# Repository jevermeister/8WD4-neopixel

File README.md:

This is a PCB which replaces the default one on Siemens 8WD4 signal tower lights with a SK6812 neopixel. 
Documentation is in the works.

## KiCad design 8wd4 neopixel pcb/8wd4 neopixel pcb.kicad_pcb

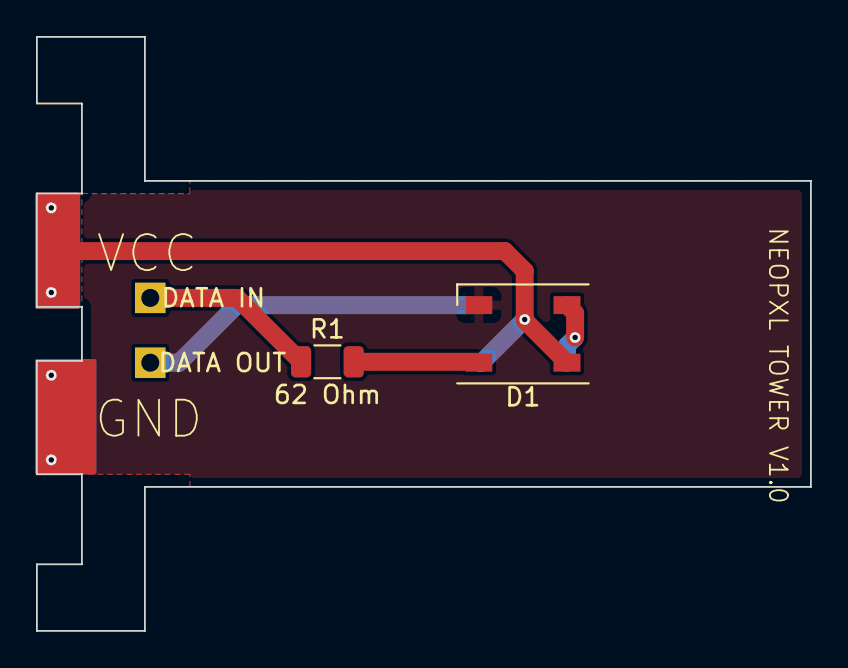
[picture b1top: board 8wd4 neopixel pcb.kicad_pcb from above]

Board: 2 copper layers, 43.0 x 33.0 mm, 5 parts (1 on the bottom side), 6 nets.

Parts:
D1, D2: SK6812; LED_SK6812_PLCC4_5.0x5.0mm_P3.2mm
DATA IN: DATA_IN; PinHeader_1x01_P2.54mm_Vertical
DATA OUT: DATA_OUT; PinHeader_1x01_P2.54mm_Vertical
R1: 62 Ohm; R_1206_3216Metric

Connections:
+5V: D1.3 (VDD), D2.3 (VDD)
GND: D1.1 (VSS), D2.1 (VSS)
unnamed: D1.2 (DIN), R1.2
unnamed: D1.4 (DOUT), D2.2 (DIN)
unnamed: D2.4 (DOUT), DATA OUT.1
unnamed: DATA IN.1, R1.1

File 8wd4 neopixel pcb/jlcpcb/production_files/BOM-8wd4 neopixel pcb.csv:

Comment,Designator,Footprint,LCSC
62 Ohm,R1,R_1206_3216Metric,
SK6812,D1,LED_SK6812_PLCC4_5.0x5.0mm_P3.2mm,
SK6812,D2,LED_SK6812_PLCC4_5.0x5.0mm_P3.2mm,

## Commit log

2024-10-17 Added initial PCB design
2024-10-17 Added license
2024-10-17 Added production files
